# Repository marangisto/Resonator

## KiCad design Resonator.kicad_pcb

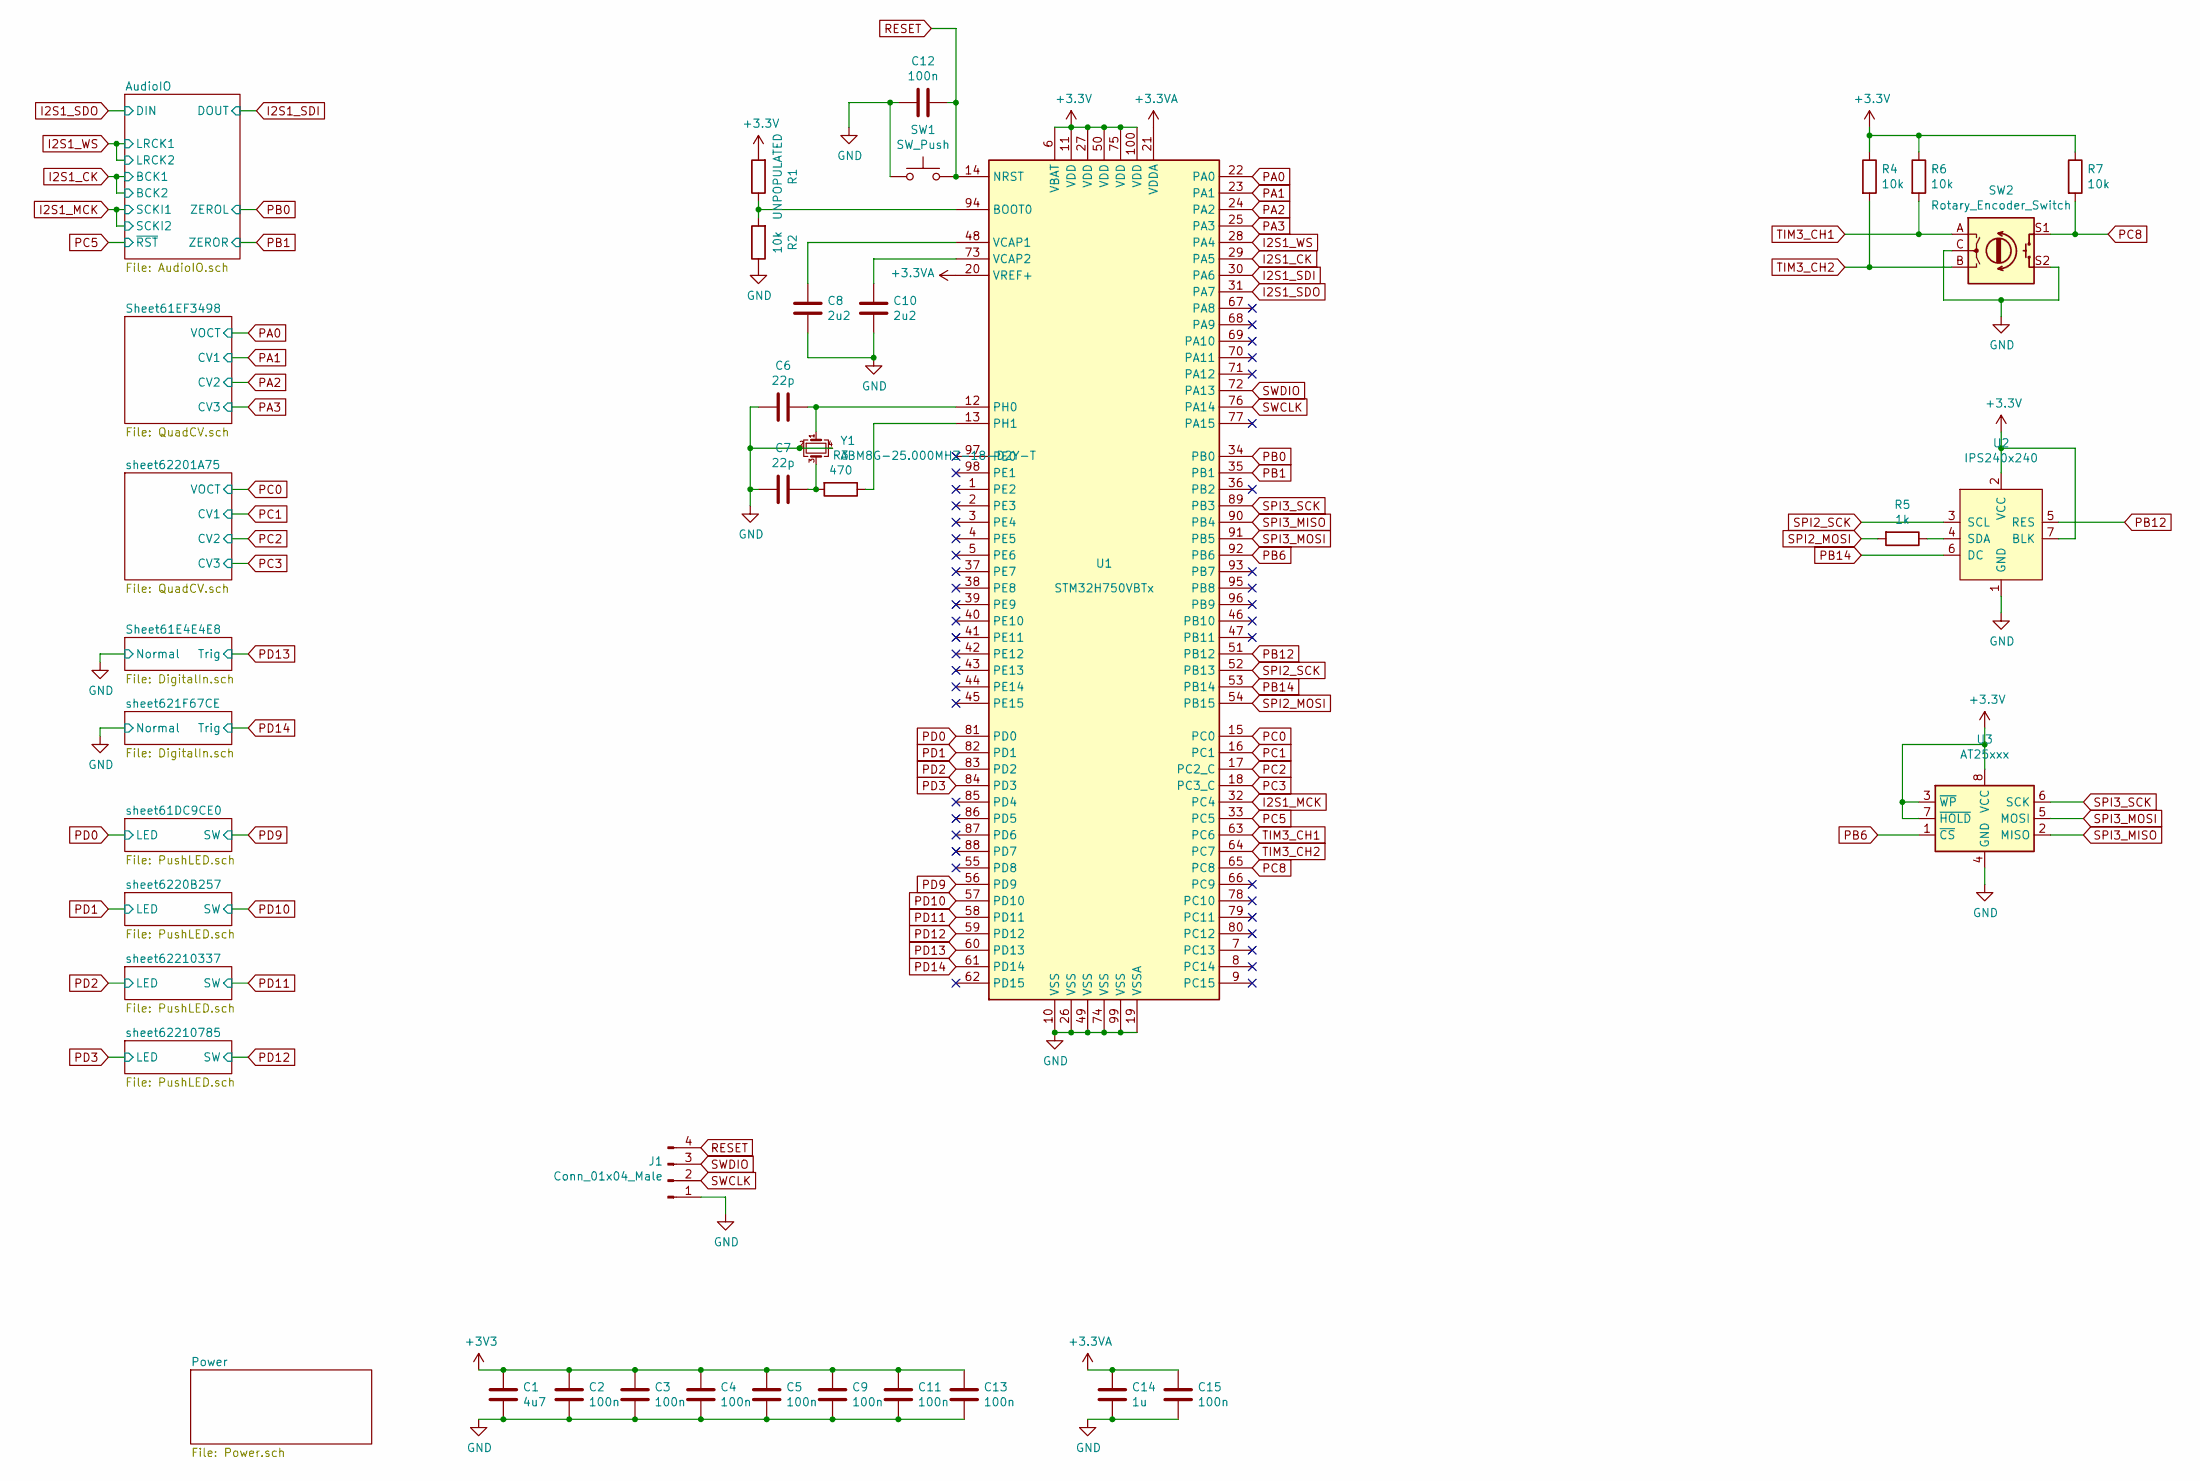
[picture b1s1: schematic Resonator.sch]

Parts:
C1: 4u7; C_0805_2012Metric
C2, C3, C4, C5, C9, C11, C12, C13, C15: 100n; C_0402_1005Metric
C6, C7: 22p; C_0402_1005Metric
C8, C10: 2u2; C_0805_2012Metric
C14: 1u; C_0805_2012Metric
J1: Conn_01x04_Male; PinHeader_1x04_P2.54mm_Vertical
R1: UNPOPULATED; R_0603_1608Metric
R2, R4, R6, R7: 10k; R_0603_1608Metric
R3: 470; R_0603_1608Metric
R5: 1k; R_0603_1608Metric
SW1: SW_Push; SW_PUSH_6mm
SW2: Rotary_Encoder_Switch; RotaryEncoder_Alps_EC11E-Switch_Vertical_H20mm
U1: STM32H750VBTx; LQFP-100_14x14mm_P0.5mm
U2: IPS240x240
U3: AT25xxx; TSSOP-8_4.4x3mm_P0.65mm
Y1: ABM8G-25.000MHZ-18-D2Y-T; Crystal_SMD_Abracon_ABM8G-4Pin_3.2x2.5mm

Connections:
+3.3VA: C14.1, C15.1, U1.20 (VREF+), U1.21 (VDDA); also elsewhere on the board
GND: C1.2, C2.2, C3.2, C4.2, C5.2, C6.2, C7.2, C8.2, C9.2, C10.2, C11.2, C12.2, C13.2, C14.2, C15.2, J1.1, R2.1, SW1.1, SW2.C, SW2.S2, U1.10 (VSS), U1.19 (VSSA), U1.26 (VSS), U1.49 (VSS), U1.74 (VSS), U1.99 (VSS), U2.1 (GND), U3.4 (GND), Y1.2, Y1.4; also elsewhere on the board
I2S1_CK: U1.29 (PA5); also elsewhere on the board
I2S1_MCK: U1.32 (PC4); also elsewhere on the board
I2S1_SDI: U1.30 (PA6); also elsewhere on the board
I2S1_SDO: U1.31 (PA7); also elsewhere on the board
I2S1_WS: U1.28 (PA4); also elsewhere on the board
unnamed: C6.1, U1.12 (PH0), Y1.1
unnamed: C7.1, R3.2, Y1.3
unnamed: C8.1, U1.48 (VCAP1)
unnamed: C10.1, U1.73 (VCAP2)
unnamed: R1.1, R2.2, U1.94 (BOOT0)
unnamed: R3.1, U1.13 (PH1)
unnamed: R5.1, U2.4 (SDA)
PA0: U1.22 (PA0); also elsewhere on the board
PA1: U1.23 (PA1); also elsewhere on the board
PA2: U1.24 (PA2); also elsewhere on the board
PA3: U1.25 (PA3); also elsewhere on the board
PB0: U1.34 (PB0); also elsewhere on the board
PB1: U1.35 (PB1); also elsewhere on the board
PB6: U1.92 (PB6), U3.1 (~CS)
PB12: U1.51 (PB12), U2.5 (RES)
PB14: U1.53 (PB14), U2.6 (DC)
PC0: U1.15 (PC0); also elsewhere on the board
PC1: U1.16 (PC1); also elsewhere on the board
PC2: U1.17 (PC2_C); also elsewhere on the board
PC3: U1.18 (PC3_C); also elsewhere on the board
PC5: U1.33 (PC5); also elsewhere on the board
PC8: R7.2, SW2.S1, U1.65 (PC8)
PD0: U1.81 (PD0); also elsewhere on the board
PD1: U1.82 (PD1); also elsewhere on the board
PD2: U1.83 (PD2); also elsewhere on the board
PD3: U1.84 (PD3); also elsewhere on the board
PD9: U1.56 (PD9); also elsewhere on the board
PD10: U1.57 (PD10); also elsewhere on the board
PD11: U1.58 (PD11); also elsewhere on the board
PD12: U1.59 (PD12); also elsewhere on the board
PD13: U1.60 (PD13); also elsewhere on the board
PD14: U1.61 (PD14); also elsewhere on the board
RESET: C12.1, J1.4, SW1.2, U1.14 (NRST)
SPI2_MOSI: R5.2, U1.54 (PB15)
SPI2_SCK: U1.52 (PB13), U2.3 (SCL)
SPI3_MISO: U1.90 (PB4), U3.2 (MISO)
SPI3_MOSI: U1.91 (PB5), U3.5 (MOSI)
SPI3_SCK: U1.89 (PB3), U3.6 (SCK)
SWCLK: J1.2, U1.76 (PA14)
SWDIO: J1.3, U1.72 (PA13)
TIM3_CH1: R6.2, SW2.A, U1.63 (PC6)
TIM3_CH2: R4.2, SW2.B, U1.64 (PC7)

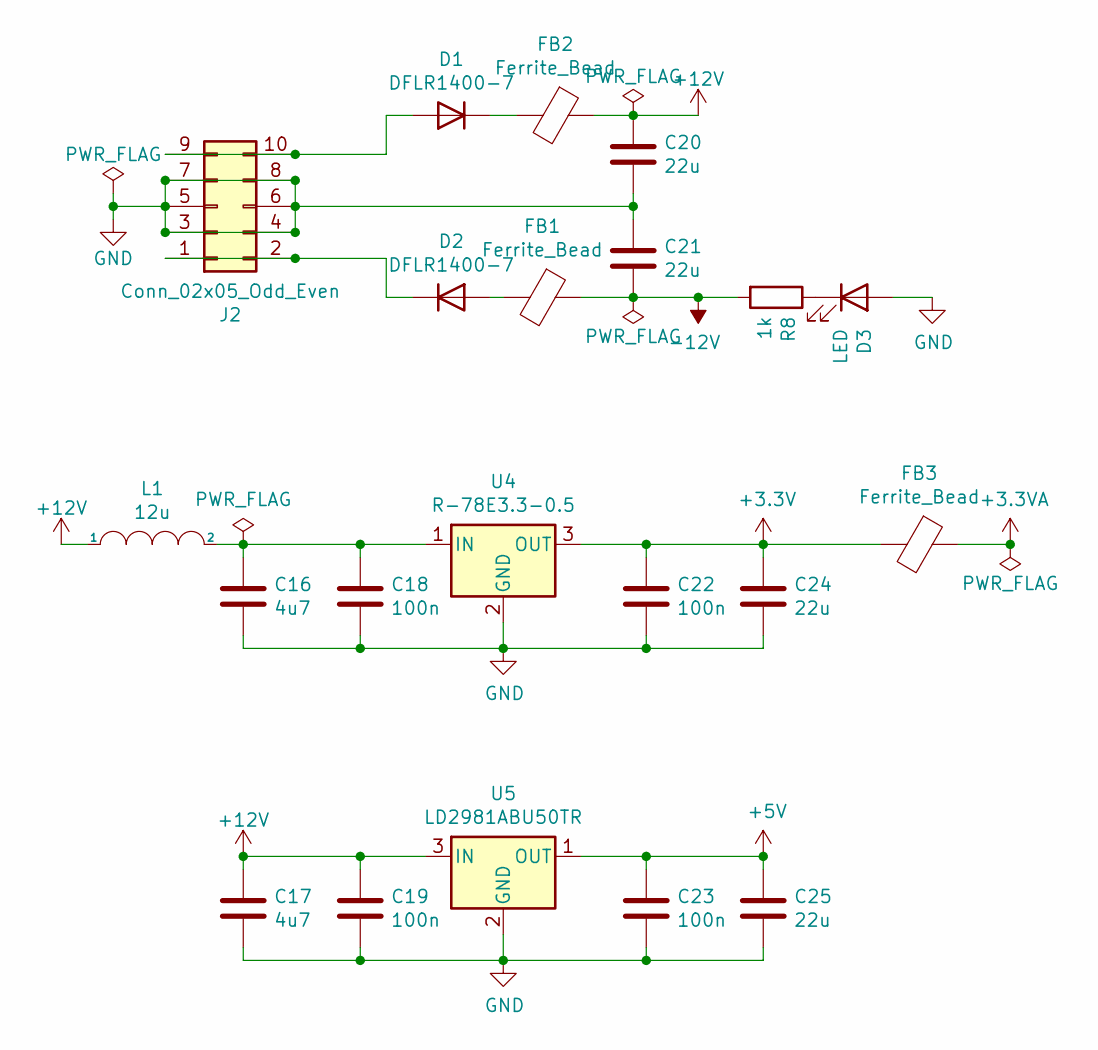
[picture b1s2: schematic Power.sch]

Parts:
C16, C17: 4u7; C_0805_2012Metric
C18, C19, C22, C23: 100n; C_0402_1005Metric
C20, C21, C24, C25: 22u; C_1206_3216Metric
D1, D2: DFLR1400-7; D_PowerDI-123
D3: LED; LED_0603_1608Metric_Castellated
FB1, FB2, FB3: Ferrite_Bead; L_0603_1608Metric
J2: Conn_02x05_Odd_Even; PinHeader_2x05_P2.54mm_Vertical
L1: 12u; L_Coilcraft_LPS3010
R8: 1k; R_0603_1608Metric
U4: R-78E3.3-0.5; Converter_DCDC_RECOM_R-78E-0.5_THT
U5: LD2981ABU50TR; SOT-89-3

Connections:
+3.3VA: FB3.1; also elsewhere on the board
+5V: C23.1, C25.1, U5.1 (OUT); also elsewhere on the board
+12V: C17.1, C19.1, C20.1, FB2.1, L1.1, U5.3 (IN); also elsewhere on the board
-12V: C21.2, FB1.1, R8.2; also elsewhere on the board
GND: C16.2, C17.2, C18.2, C19.2, C20.2, C21.1, C22.2, C23.2, C24.2, C25.2, D3.2 (A), J2.3, J2.4, J2.5, J2.6, J2.7, J2.8, U4.2 (GND), U5.2 (GND); also elsewhere on the board
unnamed: C16.1, C18.1, L1.2, U4.1 (IN)
unnamed: D1.1 (K), FB2.2
unnamed: D1.2 (A), J2.9, J2.10
unnamed: D2.1 (K), J2.1, J2.2
unnamed: D2.2 (A), FB1.2
unnamed: D3.1 (K), R8.1

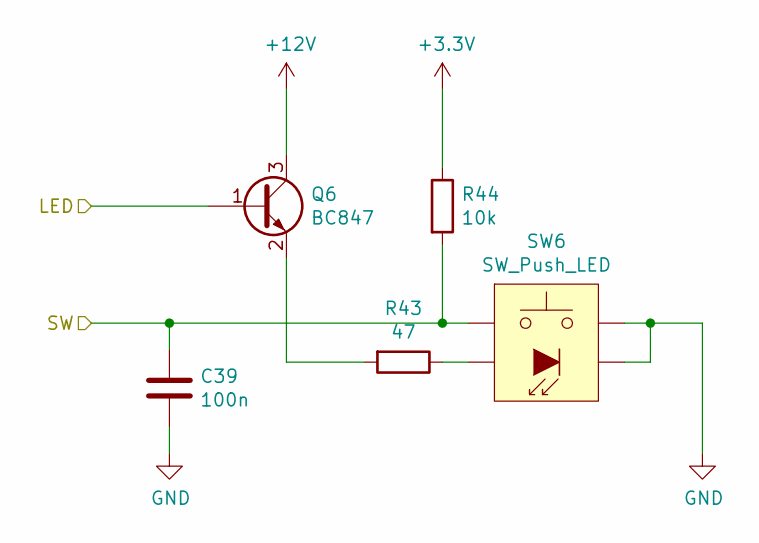
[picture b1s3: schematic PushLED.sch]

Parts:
C26: 100n; C_0402_1005Metric
Q1: BC847; SOT-23
R9: 47; R_0603_1608Metric
R10: 10k; R_0603_1608Metric
SW3: SW_Push_LED; SW_PUSH_LED_6mm

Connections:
+12V: Q1.3 (C); also elsewhere on the board
GND: C26.2, SW3.2, SW3.4 (K); also elsewhere on the board
unnamed: Q1.2 (E), R9.2
unnamed: R9.1, SW3.3 (A)
PD0: Q1.1 (B); also elsewhere on the board
PD9: C26.1, R10.2, SW3.1; also elsewhere on the board

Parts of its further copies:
C37, C38, C39: 100n; C_0402_1005Metric
Q4, Q5, Q6: BC847; SOT-23
R39, R41, R43: 47; R_0603_1608Metric
R40, R42, R44: 10k; R_0603_1608Metric
SW4, SW5, SW6: SW_Push_LED; SW_PUSH_LED_6mm

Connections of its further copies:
+12V: Q4.3 (C), Q5.3 (C), Q6.3 (C); also elsewhere on the board
GND: C37.2, C38.2, C39.2, SW4.2, SW4.4 (K), SW5.2, SW5.4 (K), SW6.2, SW6.4 (K); also elsewhere on the board
unnamed: Q4.2 (E), R39.2
unnamed: Q5.2 (E), R41.2
unnamed: Q6.2 (E), R43.2
unnamed: R39.1, SW4.3 (A)
unnamed: R41.1, SW5.3 (A)
unnamed: R43.1, SW6.3 (A)
PD1: Q4.1 (B); also elsewhere on the board
PD2: Q5.1 (B); also elsewhere on the board
PD3: Q6.1 (B); also elsewhere on the board
PD10: C37.1, R40.2, SW4.1; also elsewhere on the board
PD11: C38.1, R42.2, SW5.1; also elsewhere on the board
PD12: C39.1, R44.2, SW6.1; also elsewhere on the board

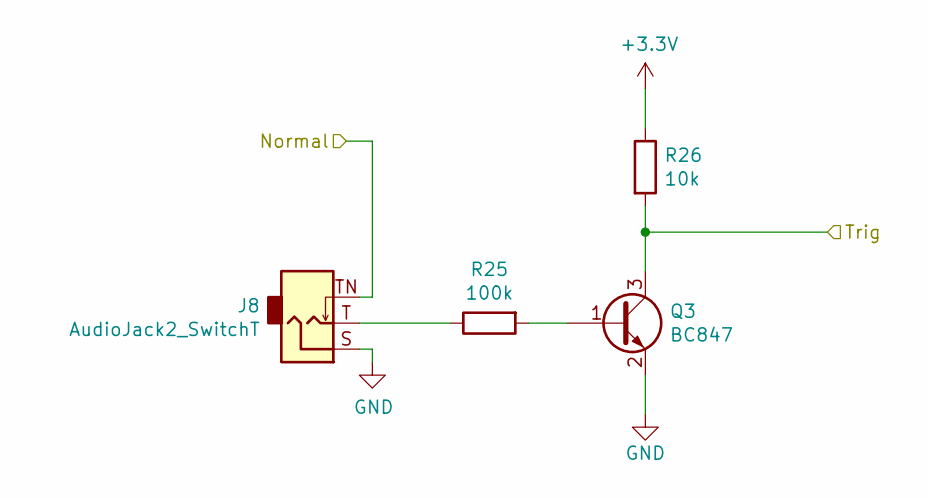
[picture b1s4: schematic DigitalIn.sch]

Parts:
J3: AudioJack2_SwitchT; PJ398SM
Q2: BC847; SOT-23
R11: 100k; R_0603_1608Metric
R12: 10k; R_0603_1608Metric

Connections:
GND: J3.S, J3.TN, Q2.2 (E); also elsewhere on the board
unnamed: J3.T, R11.1
unnamed: Q2.1 (B), R11.2
PD13: Q2.3 (C), R12.2; also elsewhere on the board

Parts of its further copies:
J8: AudioJack2_SwitchT; PJ398SM
Q3: BC847; SOT-23
R25: 100k; R_0603_1608Metric
R26: 10k; R_0603_1608Metric

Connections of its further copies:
GND: J8.S, J8.TN, Q3.2 (E); also elsewhere on the board
unnamed: J8.T, R25.1
unnamed: Q3.1 (B), R25.2
PD14: Q3.3 (C), R26.2; also elsewhere on the board

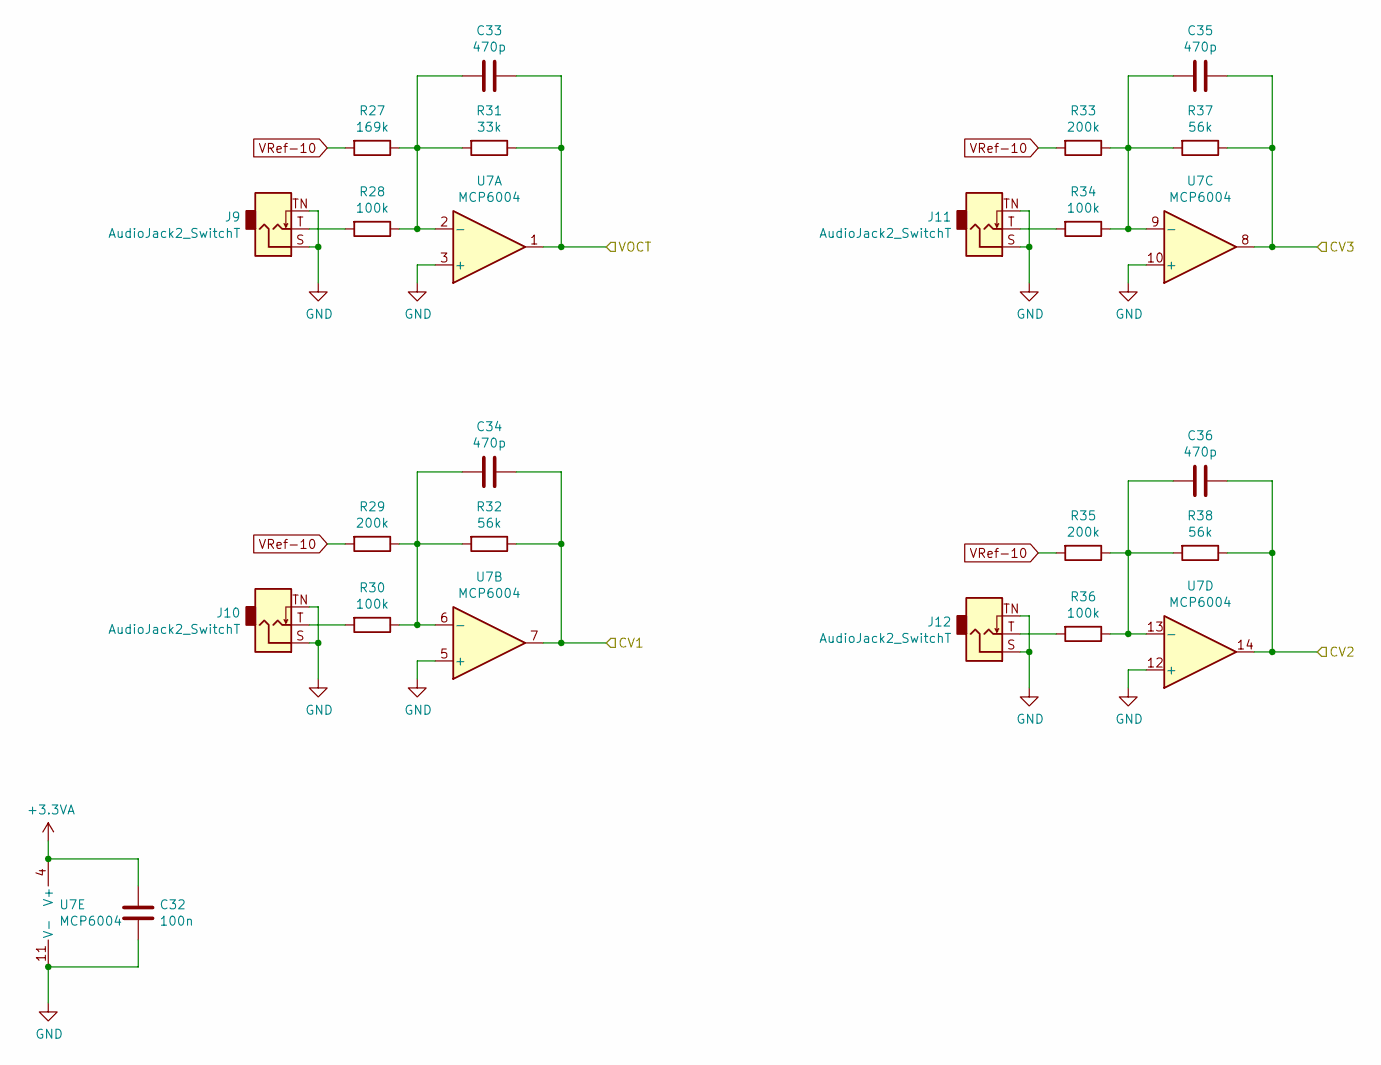
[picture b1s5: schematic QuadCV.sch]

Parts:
C27: 100n; C_0402_1005Metric
C28, C29, C30, C31: 470p; C_0603_1608Metric
J4, J5, J6, J7: AudioJack2_SwitchT; PJ398SM
R13: 169k; R_0603_1608Metric
R14, R16, R20, R22: 100k; R_0603_1608Metric
R15, R19, R21: 200k; R_0603_1608Metric
R17: 33k; R_0603_1608Metric
R18, R23, R24: 56k; R_0603_1608Metric
U6: MCP6004; TSSOP-14_4.4x5mm_P0.65mm

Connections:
+3.3VA: C27.1, U6.4 (V+); also elsewhere on the board
GND: C27.2, J4.S, J4.TN, J5.S, J5.TN, J6.S, J6.TN, J7.S, J7.TN, U6.3 (+), U6.5 (+), U6.10 (+), U6.11 (V-), U6.12 (+); also elsewhere on the board
unnamed: C28.2, R13.1, R14.1, R17.2, U6.2 (-)
unnamed: C29.2, R15.1, R16.1, R18.2, U6.6 (-)
unnamed: C30.2, R19.1, R20.1, R23.2, U6.9 (-)
unnamed: C31.2, R21.1, R22.1, R24.2, U6.13 (-)
unnamed: J4.T, R14.2
unnamed: J5.T, R16.2
unnamed: J6.T, R20.2
unnamed: J7.T, R22.2
PA0: C28.1, R17.1, U6.1; also elsewhere on the board
PA1: C29.1, R18.1, U6.7; also elsewhere on the board
PA2: C31.1, R24.1, U6.14; also elsewhere on the board
PA3: C30.1, R23.1, U6.8; also elsewhere on the board
VRef-10: R13.2, R15.2, R19.2, R21.2; also elsewhere on the board

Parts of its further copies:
C32: 100n; C_0402_1005Metric
C33, C34, C35, C36: 470p; C_0603_1608Metric
J9, J10, J11, J12: AudioJack2_SwitchT; PJ398SM
R27: 169k; R_0603_1608Metric
R28, R30, R34, R36: 100k; R_0603_1608Metric
R29, R33, R35: 200k; R_0603_1608Metric
R31: 33k; R_0603_1608Metric
R32, R37, R38: 56k; R_0603_1608Metric
U7: MCP6004; TSSOP-14_4.4x5mm_P0.65mm

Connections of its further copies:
+3.3VA: C32.1, U7.4 (V+); also elsewhere on the board
GND: C32.2, J9.S, J9.TN, J10.S, J10.TN, J11.S, J11.TN, J12.S, J12.TN, U7.3 (+), U7.5 (+), U7.10 (+), U7.11 (V-), U7.12 (+); also elsewhere on the board
unnamed: C33.2, R27.1, R28.1, R31.2, U7.2 (-)
unnamed: C34.2, R29.1, R30.1, R32.2, U7.6 (-)
unnamed: C35.2, R33.1, R34.1, R37.2, U7.9 (-)
unnamed: C36.2, R35.1, R36.1, R38.2, U7.13 (-)
unnamed: J9.T, R28.2
unnamed: J10.T, R30.2
unnamed: J11.T, R34.2
unnamed: J12.T, R36.2
PC0: C33.1, R31.1, U7.1; also elsewhere on the board
PC1: C34.1, R32.1, U7.7; also elsewhere on the board
PC2: C36.1, R38.1, U7.14; also elsewhere on the board
PC3: C35.1, R37.1, U7.8; also elsewhere on the board
VRef-10: R27.2, R29.2, R33.2, R35.2; also elsewhere on the board

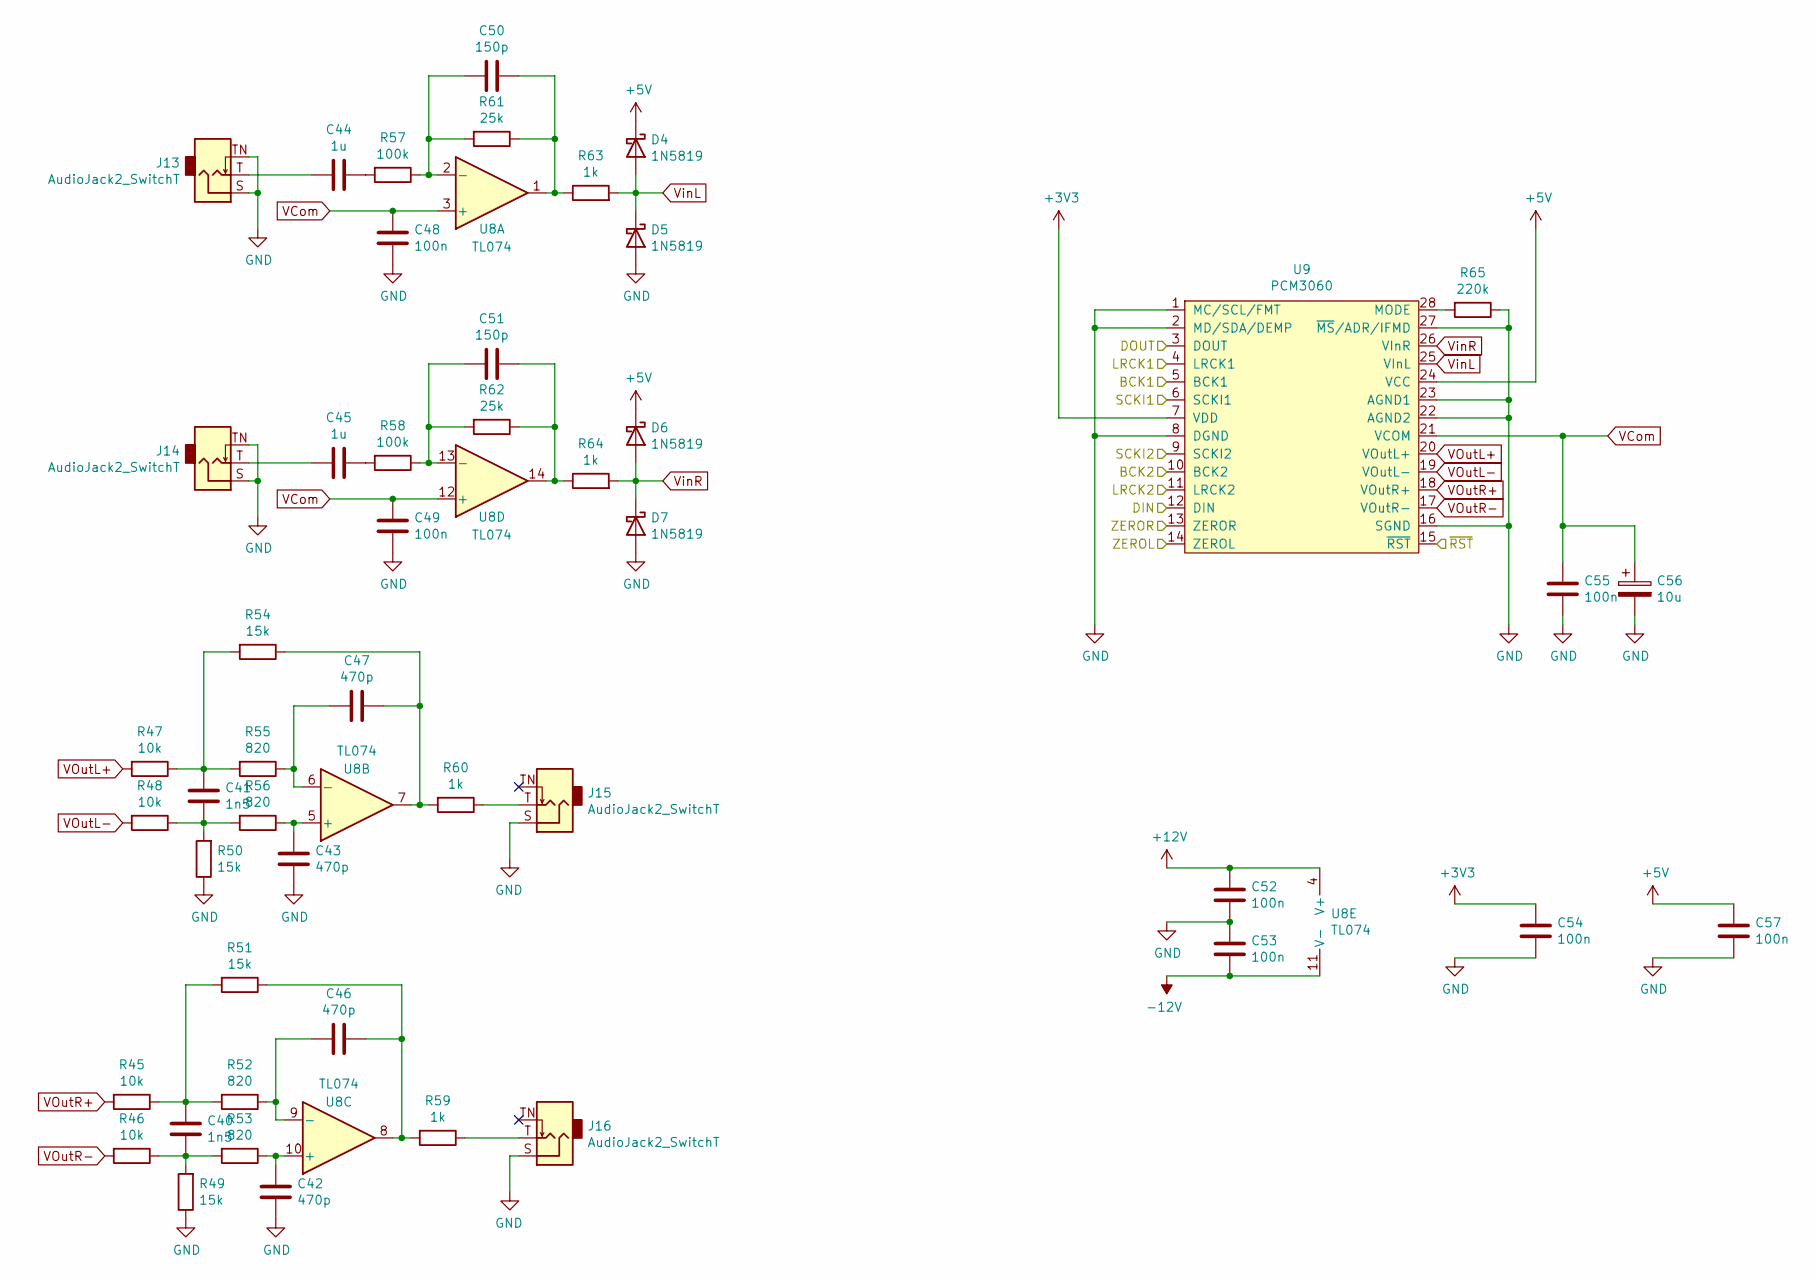
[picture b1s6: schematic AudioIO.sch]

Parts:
C40, C41: 1n5; C_0603_1608Metric
C42, C43, C46, C47: 470p; C_0603_1608Metric
C44, C45: 1u; C_1210_3225Metric
C48, C49, C52, C53, C54, C55, C57: 100n; C_0402_1005Metric
C50, C51: 150p; C_0603_1608Metric
C56: 10u; C_0603_1608Metric
D4, D5, D6, D7: 1N5819; D_SOD-123
J13, J14, J15, J16: AudioJack2_SwitchT; PJ398SM
R45, R46, R47, R48: 10k; R_0603_1608Metric
R49, R50, R51, R54: 15k; R_0603_1608Metric
R52, R53, R55, R56: 820; R_0603_1608Metric
R57, R58: 100k; R_0603_1608Metric
R59, R60, R63, R64: 1k; R_0603_1608Metric
R61, R62: 25k; R_0603_1608Metric
R65: 220k; R_0603_1608Metric
U8: TL074; TSSOP-14_4.4x5mm_P0.65mm
U9: PCM3060; TSSOP-28_4.4x9.7mm_P0.65mm

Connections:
+5V: C57.1, D4.1 (K), D6.1 (K), U9.24 (VCC); also elsewhere on the board
+12V: C52.1, U8.4 (V+); also elsewhere on the board
-12V: C53.2, U8.11 (V-); also elsewhere on the board
GND: C42.2, C43.2, C48.2, C49.2, C52.2, C53.1, C54.2, C55.2, C56.2, C57.2, D5.2 (A), D7.2 (A), J13.S, J13.TN, J14.S, J14.TN, J15.S, J16.S, R49.1, R50.1, R65.1, U9.1 (MC/SCL/FMT), U9.2 (MD/SDA/DEMP), U9.8 (DGND), U9.16 (SGND), U9.22 (AGND2), U9.23 (AGND1), U9.27 (~MS~/ADR/IFMD); also elsewhere on the board
I2S1_CK: U9.5 (BCK1), U9.10 (BCK2); also elsewhere on the board
I2S1_MCK: U9.6 (SCKI1), U9.9 (SCKI2); also elsewhere on the board
I2S1_SDI: U9.3 (DOUT); also elsewhere on the board
I2S1_SDO: U9.12 (DIN); also elsewhere on the board
I2S1_WS: U9.4 (LRCK1), U9.11 (LRCK2); also elsewhere on the board
unnamed: C40.1, R45.1, R51.2, R52.2
unnamed: C40.2, R46.1, R49.2, R53.2
unnamed: C41.1, R47.1, R54.2, R55.2
unnamed: C41.2, R48.1, R50.2, R56.2
unnamed: C42.1, R53.1, U8.10 (+)
unnamed: C43.1, R56.1, U8.5 (+)
unnamed: C44.1, R57.2
unnamed: C44.2, J13.T
unnamed: C45.1, R58.2
unnamed: C45.2, J14.T
unnamed: C46.1, R51.1, R59.2, U8.8
unnamed: C46.2, R52.1, U8.9 (-)
unnamed: C47.1, R54.1, R60.2, U8.7
unnamed: C47.2, R55.1, U8.6 (-)
unnamed: C50.1, R61.1, R63.1, U8.1
unnamed: C50.2, R57.1, R61.2, U8.2 (-)
unnamed: C51.1, R62.1, R64.1, U8.14
unnamed: C51.2, R58.1, R62.2, U8.13 (-)
unnamed: J15.T, R60.1
unnamed: J16.T, R59.1
unnamed: R65.2, U9.28 (MODE)
PB0: U9.14 (ZEROL); also elsewhere on the board
PB1: U9.13 (ZEROR); also elsewhere on the board
PC5: U9.15 (~RST); also elsewhere on the board
VCom: C48.1, C49.1, C55.1, C56.1, U8.3 (+), U8.12 (+), U9.21 (VCOM)
VOutL+: R47.2, U9.20 (VOutL+)
VOutL-: R48.2, U9.19 (VOutL-)
VOutR+: R45.2, U9.18 (VOutR+)
VOutR-: R46.2, U9.17 (VOutR-)
VinL: D4.2 (A), D5.1 (K), R63.2, U9.25 (VInL)
VinR: D6.2 (A), D7.1 (K), R64.2, U9.26 (VInR)

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
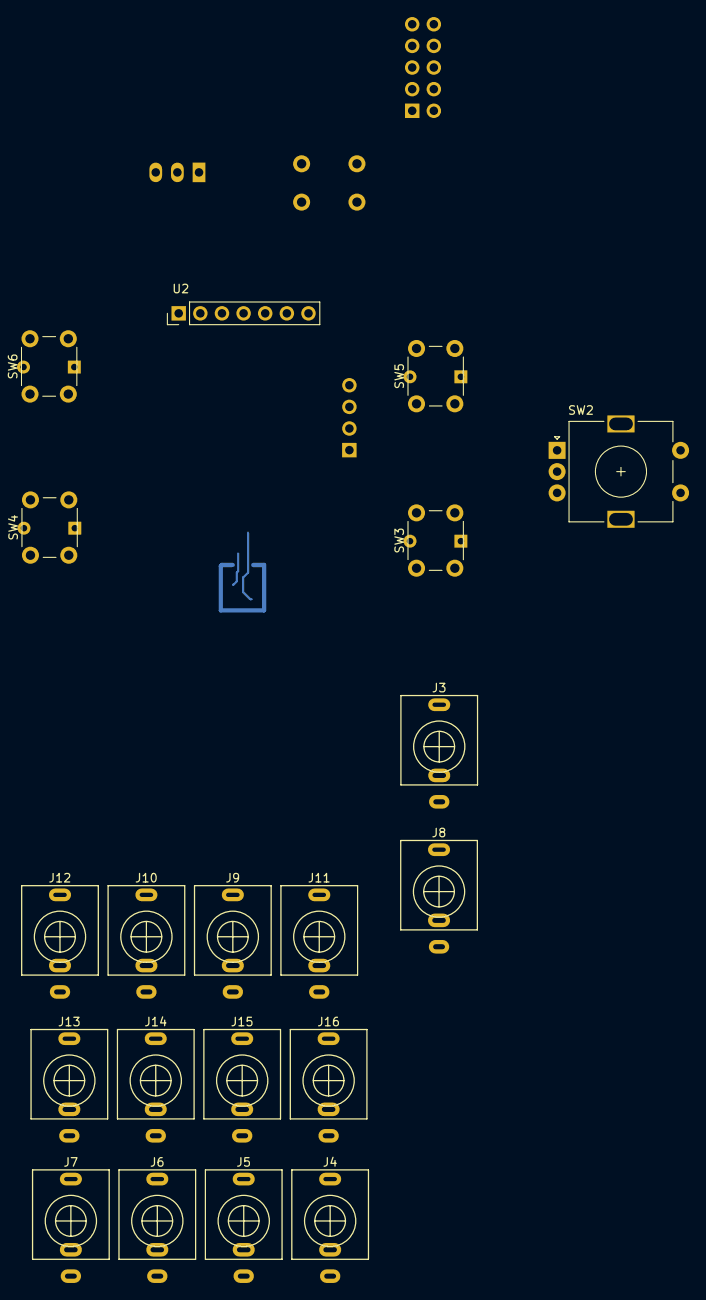
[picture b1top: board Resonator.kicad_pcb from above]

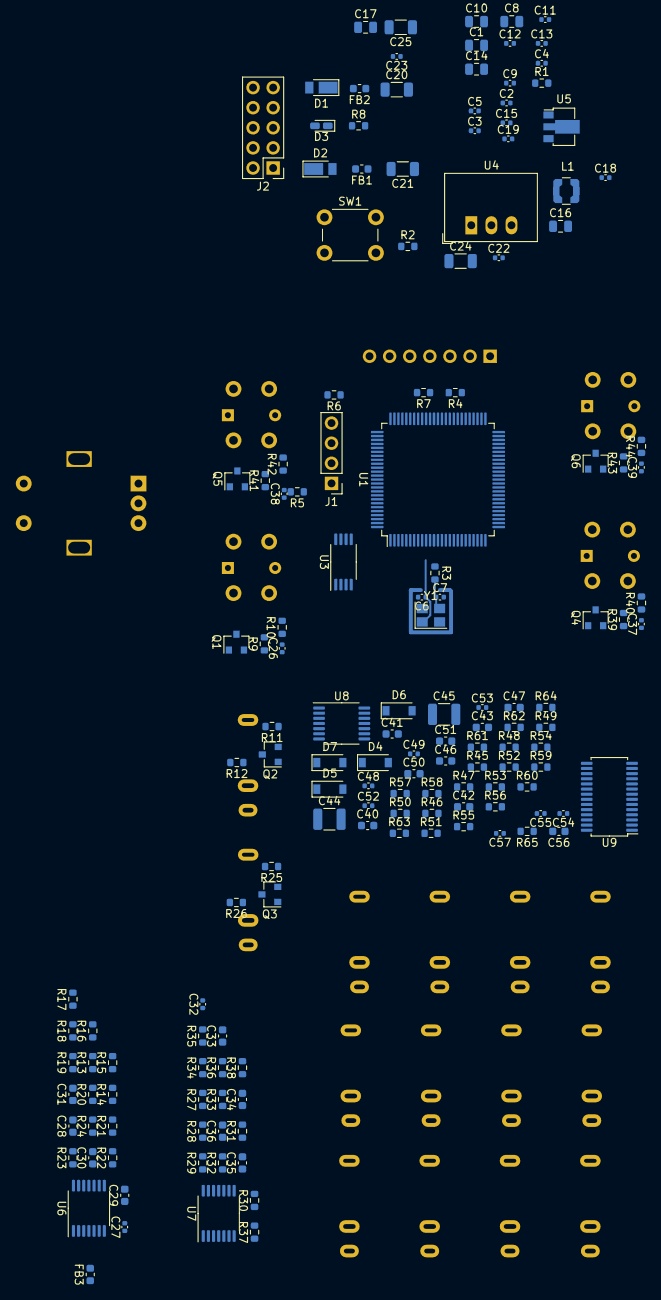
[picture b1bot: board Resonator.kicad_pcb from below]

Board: 2 copper layers, 171 parts (151 on the bottom side), 116 nets.

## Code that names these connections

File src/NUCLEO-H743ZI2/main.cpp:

#include "board.h"
#include <i2s.h>
#include <dma.h>
#include <fixed.h>
#include <cstring>
#include <textio.h>
#include <usart.h>
//#include <adc.h>

using namespace fixed;

using led = output_t<LED>;
using probe = output_t<PA7>;
using reset = output_t<PB4>;
//using adc = adc_t<1>;
using a0 = analog_t<A0>;
using a1 = analog_t<A1>;
using serial = usart_t<SERIAL_USART, SERIAL_TX, SERIAL_RX>;
using in_i2s = i2s_t<2, master_receiver, PB10, PB14, PB12, PC6>;
using out_i2s = i2s_t<3, master_transmitter, PB3, PB5, PA4, PC7>;
using dma = dma_t<1>;

static const unsigned in_dma_ch = 1;
static const unsigned out_dma_ch = 2;
static const uint16_t half_samples = 64;                // half number of samples
static const uint16_t n_samples = half_samples << 1;    // number of samples
static const unsigned buf_size = n_samples << 1;        // we have two channels
static int32_t in_buf[buf_size], out_buf[buf_size];     // i/o sample buffers
static volatile bool target_upper_half = false;         // where to write output
static volatile q31_t lVolume(.0), rVolume(.0);         // volume controls

static inline uint32_t swap(uint32_t x)
{
    return (x >> 16) | (x << 16);
}

template<> void handler<SERIAL_ISR>()
{
    serial::isr();
}

template<> void handler<interrupt::DMA1_CH1>()
{
    probe::set();

    auto sts = dma::interrupt_status<in_dma_ch>();
    dma::clear_interrupt_flags<in_dma_ch>();

    if (sts & (dma_half_transfer | dma_transfer_complete))
    {
        int32_t *src = in_buf + (sts & dma_transfer_complete ? n_samples : 0);
        int32_t *dst = out_buf + (target_upper_half ? n_samples : 0);

        for (uint16_t i = 0; i < half_samples; ++i)
        {
            q31_t l(static_cast<int32_t>(swap(*src++)));
            q31_t r(static_cast<int32_t>(swap(*src++)));

            *dst++ = swap((l * lVolume).q);
            *dst++ = swap((r * rVolume).q);
        }
    }

    probe::clear();
}

template<> void handler<interrupt::DMA1_CH2>()
{
    auto sts = dma::interrupt_status<out_dma_ch>();
    dma::clear_interrupt_flags<out_dma_ch>();

    if (sts & (dma_half_transfer | dma_transfer_complete))
        target_upper_half = sts & dma_transfer_complete;
}

int main()
{
    led::setup();
    probe::setup();
    reset::setup();
    reset::set();       // active low

    a0::setup();
    a1::setup();
    //adc::setup();
    //adc::enable();

    serial::setup<230400>();
    interrupt::set<SERIAL_ISR>();
    interrupt::enable();

    printf<serial>("Welcome to I2S!\n");
    printf<serial>("sys-clock = %d\n", sys_clock::freq());

    dma::setup();

    in_i2s::setup<philips_i2s, low_level, format_32_32, 17>();
    in_i2s::enable_dma<dma, in_dma_ch>(reinterpret_cast<uint16_t*>(in_buf), buf_size << 1);
    dma::enable_interrupt<in_dma_ch, true>();
    interrupt::set<interrupt::DMA1_CH1>();

    out_i2s::setup<philips_i2s, low_level, format_32_32, 17>();
    out_i2s::enable_dma<dma, out_dma_ch>(reinterpret_cast<uint16_t*>(out_buf), buf_size << 1);
    dma::enable_interrupt<out_dma_ch, true>();
    interrupt::set<interrupt::DMA1_CH2>();

    for (;;)
    {
        float x0 = 1.; // (1. / 4096.) * adc::read<a0>();
        float x1 = 1.; // (1. / 4096.) * adc::read<a1>();

        lVolume = q31_t(x0);
        rVolume = q31_t(x1);

        printf<serial>("%0.2f %40.2f\n", x0, x1);
        led::toggle();
        sys_tick::delay_ms(250);
    }
}

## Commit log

2021-11-21 Skeleton project.
2021-11-21 Added PCM3060 symbol and initial wiring.
2021-11-22 More work on basic configuraiton of CODEC.
2021-11-23 All pins assigned and working.
2021-11-23 Corrected reset pin assignment.
2021-11-25 Full input / output pipeline working.
2021-11-27 Added input stage spice simulation.
2021-11-27 Added input stages to schema.
2021-11-28 Added output stage spice simulation.
2021-11-28 Output stage schematic.
2021-11-28 Some early placement.
2021-11-28 Added power supply and adjusted gains for 12Vpp I/O.
2021-11-29 Moved audio-io to separate sheet.
2021-11-29 Added STM32750 mcu.
2021-12-04 Chanced regulators and oscillator work.
2022-01-08 Added library resources.
2022-01-09 Reusable digital input.
2022-01-09 Reusable Quad CV input module.
2022-01-09 Added UI components.
2022-01-09 Moved codec to audio module.
2022-01-10 Re-annotation.
2022-01-10 Assigned pins and cleared schema rules.
